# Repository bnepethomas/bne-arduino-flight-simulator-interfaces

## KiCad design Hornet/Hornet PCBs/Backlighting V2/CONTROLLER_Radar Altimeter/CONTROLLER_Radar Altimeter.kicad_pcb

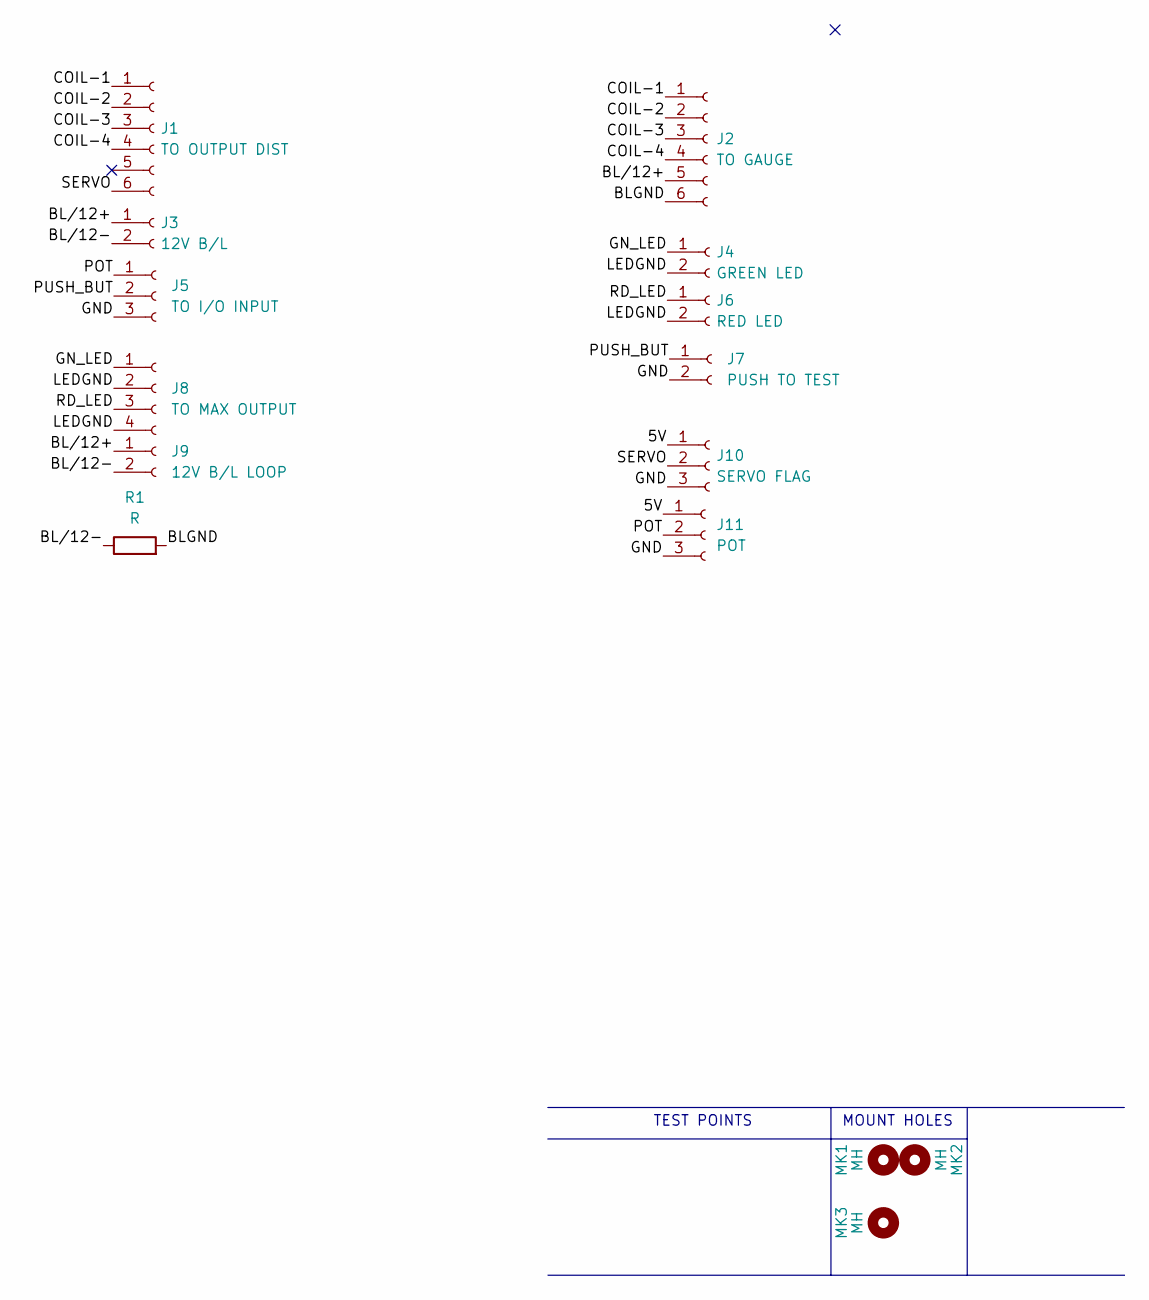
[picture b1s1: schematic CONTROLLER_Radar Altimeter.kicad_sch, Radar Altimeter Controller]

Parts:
J1: TO OUTPUT DIST; Molex_KK-254_AE-6410-06A_1x06_P2.54mm_Vertical
J2: TO GAUGE; Molex_KK-254_AE-6410-06A_1x06_P2.54mm_Vertical
J3: 12V B/L; Molex_KK-254_AE-6410-02A_1x02_P2.54mm_Vertical
J4: GREEN LED; Molex_KK-254_AE-6410-02A_1x02_P2.54mm_Vertical
J5: TO I/O INPUT; Molex_KK-254_AE-6410-03A_1x03_P2.54mm_Vertical
J6: RED LED; Molex_KK-254_AE-6410-02A_1x02_P2.54mm_Vertical
J7: PUSH TO TEST; Molex_KK-254_AE-6410-02A_1x02_P2.54mm_Vertical
J8: TO MAX OUTPUT; Molex_KK-254_AE-6410-04A_1x04_P2.54mm_Vertical
J9: 12V B/L LOOP; Molex_KK-254_AE-6410-02A_1x02_P2.54mm_Vertical
J10: SERVO FLAG; Molex_KK-254_AE-6410-03A_1x03_P2.54mm_Vertical
J11: POT; Molex_KK-254_AE-6410-03A_1x03_P2.54mm_Vertical
MK1, MK2, MK3: MH; MountingHole_2.5mm
R1: R; R_Axial_DIN0204_L3.6mm_D1.6mm_P2.54mm_Vertical

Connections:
/5V: J10.1, J11.1
/BLGND: J2.6, R1.2
/BL/12+: J2.5, J3.1, J9.1
/BL/12-: J3.2, J9.2, R1.1
/COIL-1: J1.1, J2.1
/COIL-2: J1.2, J2.2
/COIL-3: J1.3, J2.3
/COIL-4: J1.4, J2.4
/GND: J5.3, J7.2, J10.3, J11.3
/GN_LED: J4.1, J8.1
/LEDGND: J4.2, J6.2, J8.2, J8.4
/POT: J5.1, J11.2
/PUSH_BUT: J5.2, J7.1
/RD_LED: J6.1, J8.3
/SERVO: J1.6, J10.2

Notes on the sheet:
MOUNT HOLES
TEST POINTS

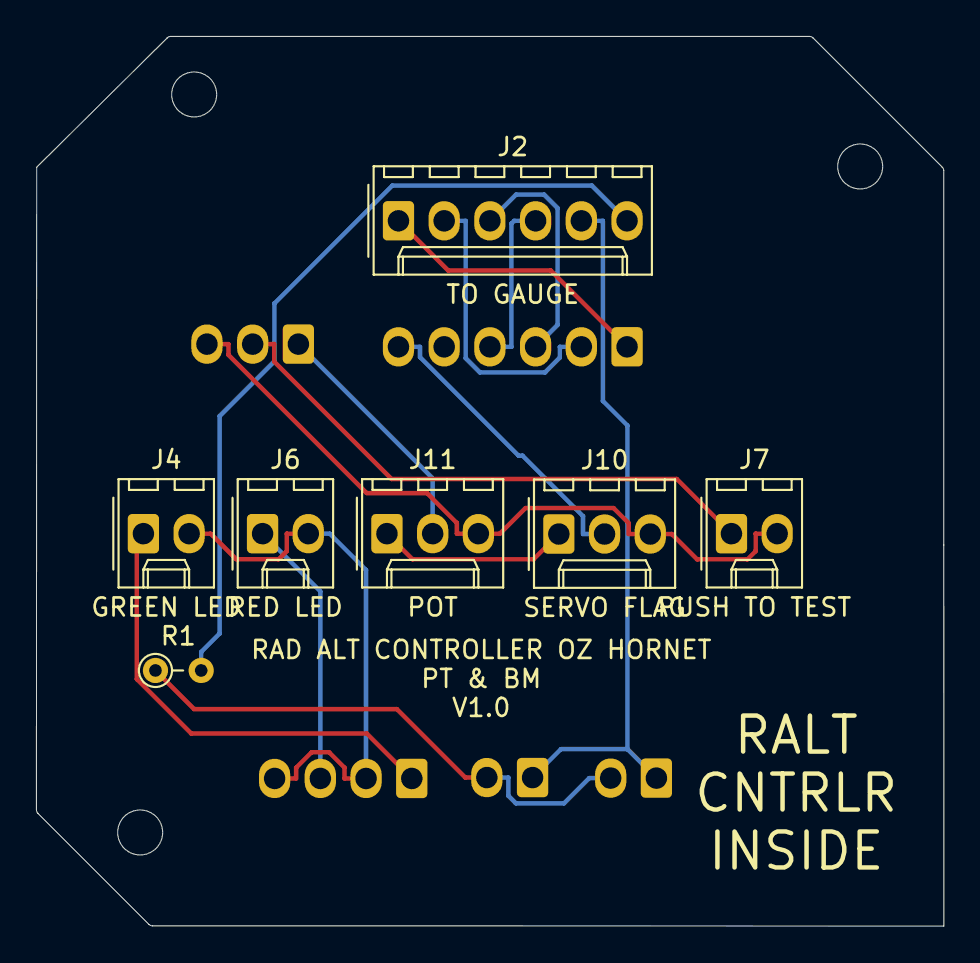
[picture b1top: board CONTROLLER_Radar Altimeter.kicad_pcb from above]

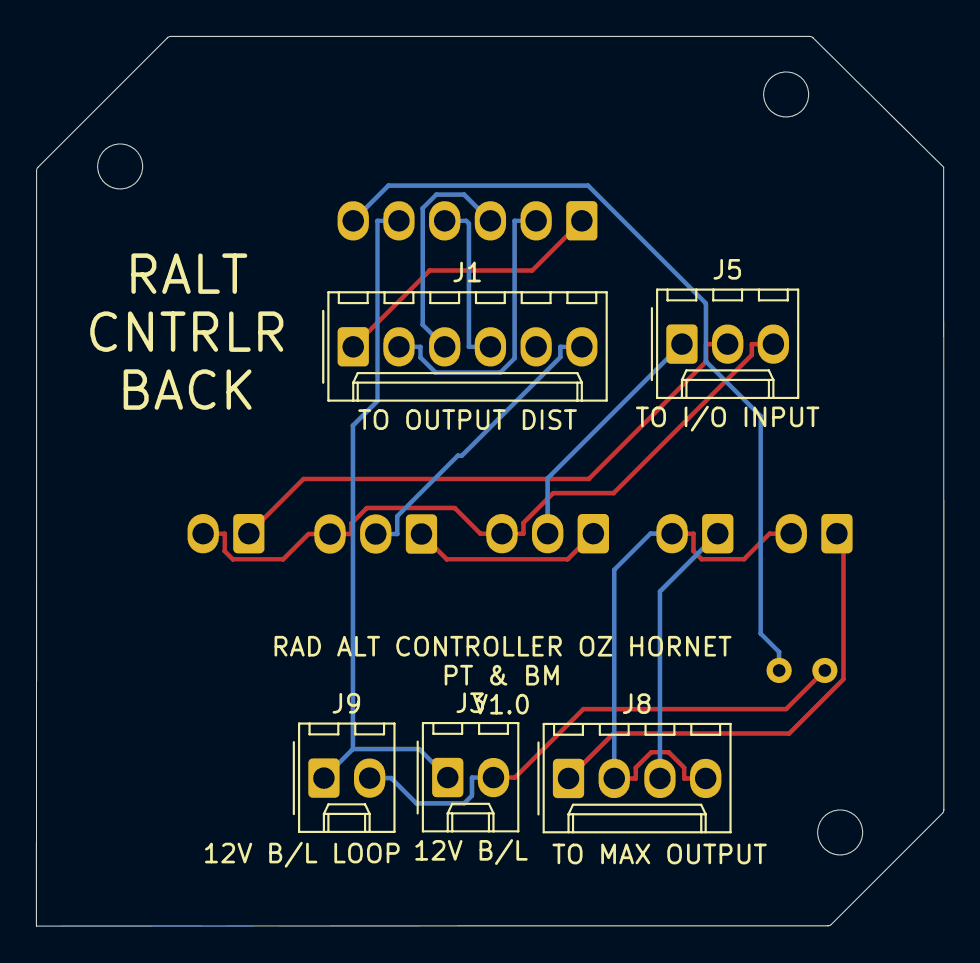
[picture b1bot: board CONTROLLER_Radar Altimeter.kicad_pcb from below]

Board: 2 copper layers, 50.4 x 49.4 mm, 15 parts (5 on the bottom side), 15 nets.

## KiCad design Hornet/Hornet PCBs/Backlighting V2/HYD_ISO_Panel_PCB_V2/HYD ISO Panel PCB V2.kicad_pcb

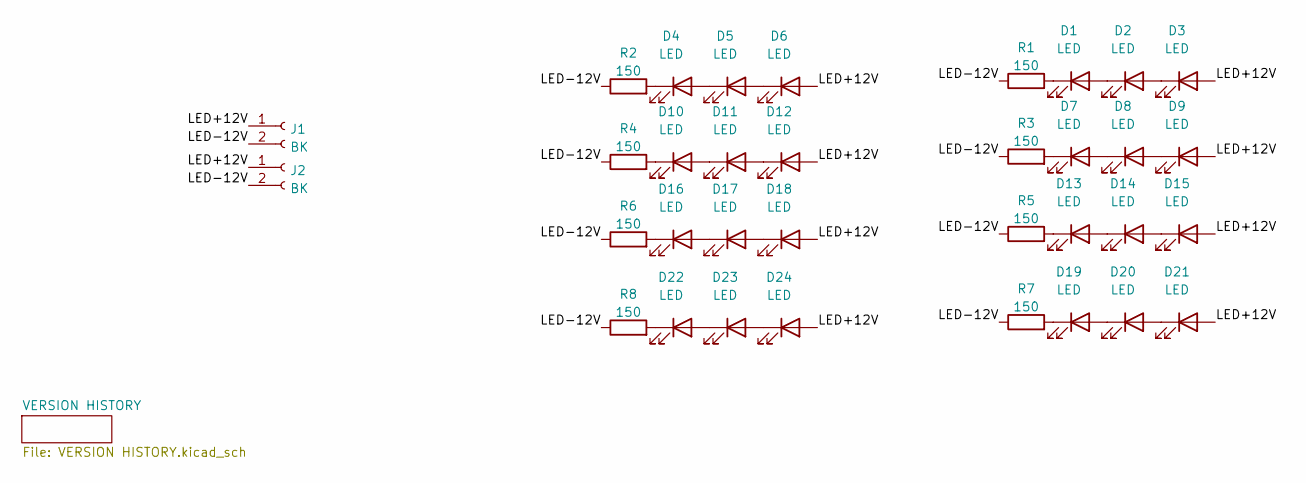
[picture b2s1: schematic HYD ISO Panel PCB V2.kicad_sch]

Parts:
D1, D2, D3, D4, D5, D6, D7, D8, D9, D10, D11, D12, D13, D14, D15, D16, D17, D18, D19, D20, D21, D22, D23, D24: LED; LED_D3.0mm
J1, J2: BK; Molex_KK-254_AE-6410-02A_1x02_P2.54mm_Vertical
R1, R2, R3, R4, R5, R6, R7, R8: 150; R_Axial_DIN0204_L3.6mm_D1.6mm_P2.54mm_Vertical

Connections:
/LED+12V: D3.2 (A), D6.2 (A), D9.2 (A), D12.2 (A), D15.2 (A), D18.2 (A), D21.2 (A), D24.2 (A), J1.1, J2.1
/LED-12V: J1.2, J2.2, R1.1, R2.1, R3.1, R4.1, R5.1, R6.1, R7.1, R8.1
unnamed: D1.1 (K), R1.2
unnamed: D1.2 (A), D2.1 (K)
unnamed: D2.2 (A), D3.1 (K)
unnamed: D4.1 (K), R2.2
unnamed: D4.2 (A), D5.1 (K)
unnamed: D5.2 (A), D6.1 (K)
unnamed: D7.1 (K), R3.2
unnamed: D7.2 (A), D8.1 (K)
unnamed: D8.2 (A), D9.1 (K)
unnamed: D10.1 (K), R4.2
unnamed: D10.2 (A), D11.1 (K)
unnamed: D11.2 (A), D12.1 (K)
unnamed: D13.1 (K), R5.2
unnamed: D13.2 (A), D14.1 (K)
unnamed: D14.2 (A), D15.1 (K)
unnamed: D16.1 (K), R6.2
unnamed: D16.2 (A), D17.1 (K)
unnamed: D17.2 (A), D18.1 (K)
unnamed: D19.1 (K), R7.2
unnamed: D19.2 (A), D20.1 (K)
unnamed: D20.2 (A), D21.1 (K)
unnamed: D22.1 (K), R8.2
unnamed: D22.2 (A), D23.1 (K)
unnamed: D23.2 (A), D24.1 (K)

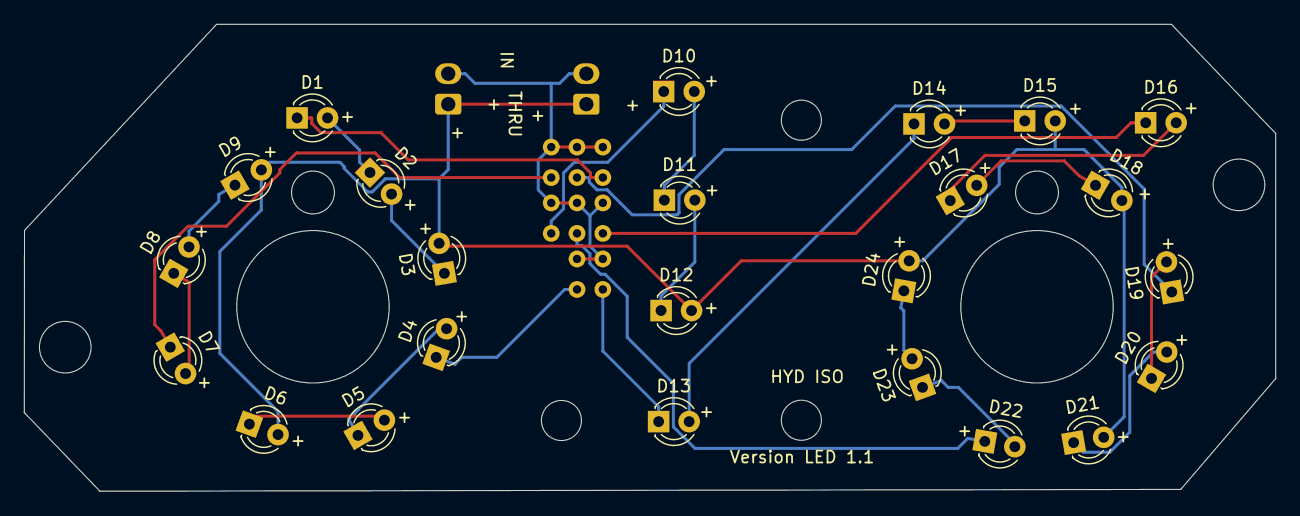
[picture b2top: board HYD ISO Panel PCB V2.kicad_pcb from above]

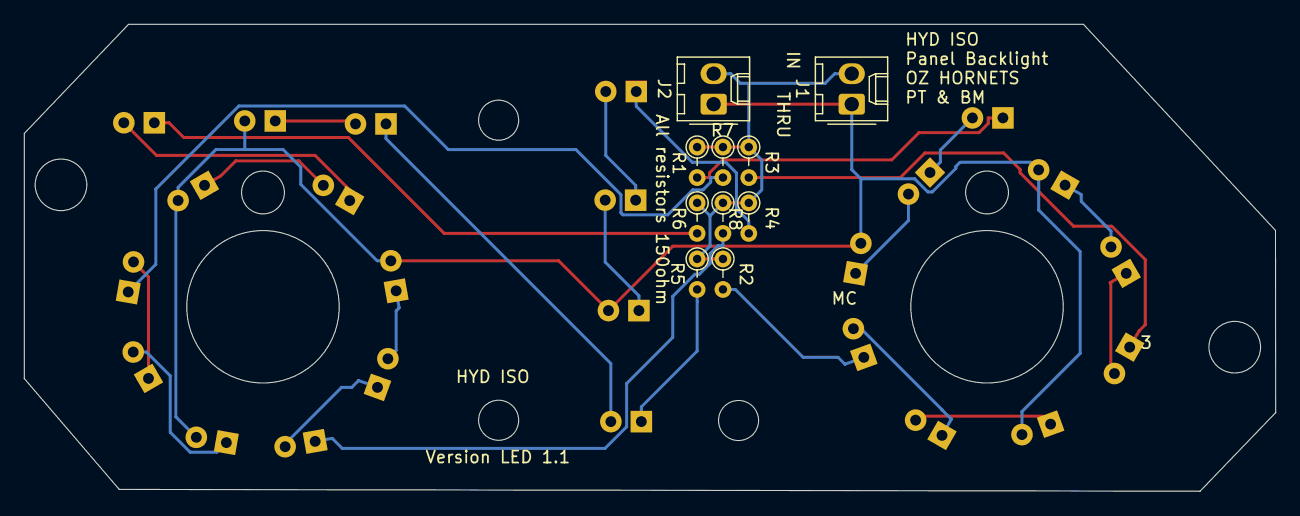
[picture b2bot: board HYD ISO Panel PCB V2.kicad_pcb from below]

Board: 2 copper layers, 104.3 x 38.9 mm, 38 parts (10 on the bottom side), 26 nets.

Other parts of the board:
REF01, REF02: OH_Panel_Fastner_Keepout; OH_Panel_6-32_PHS
REF03, REF04: 100SPX_Toggle_13mm_x_18mm

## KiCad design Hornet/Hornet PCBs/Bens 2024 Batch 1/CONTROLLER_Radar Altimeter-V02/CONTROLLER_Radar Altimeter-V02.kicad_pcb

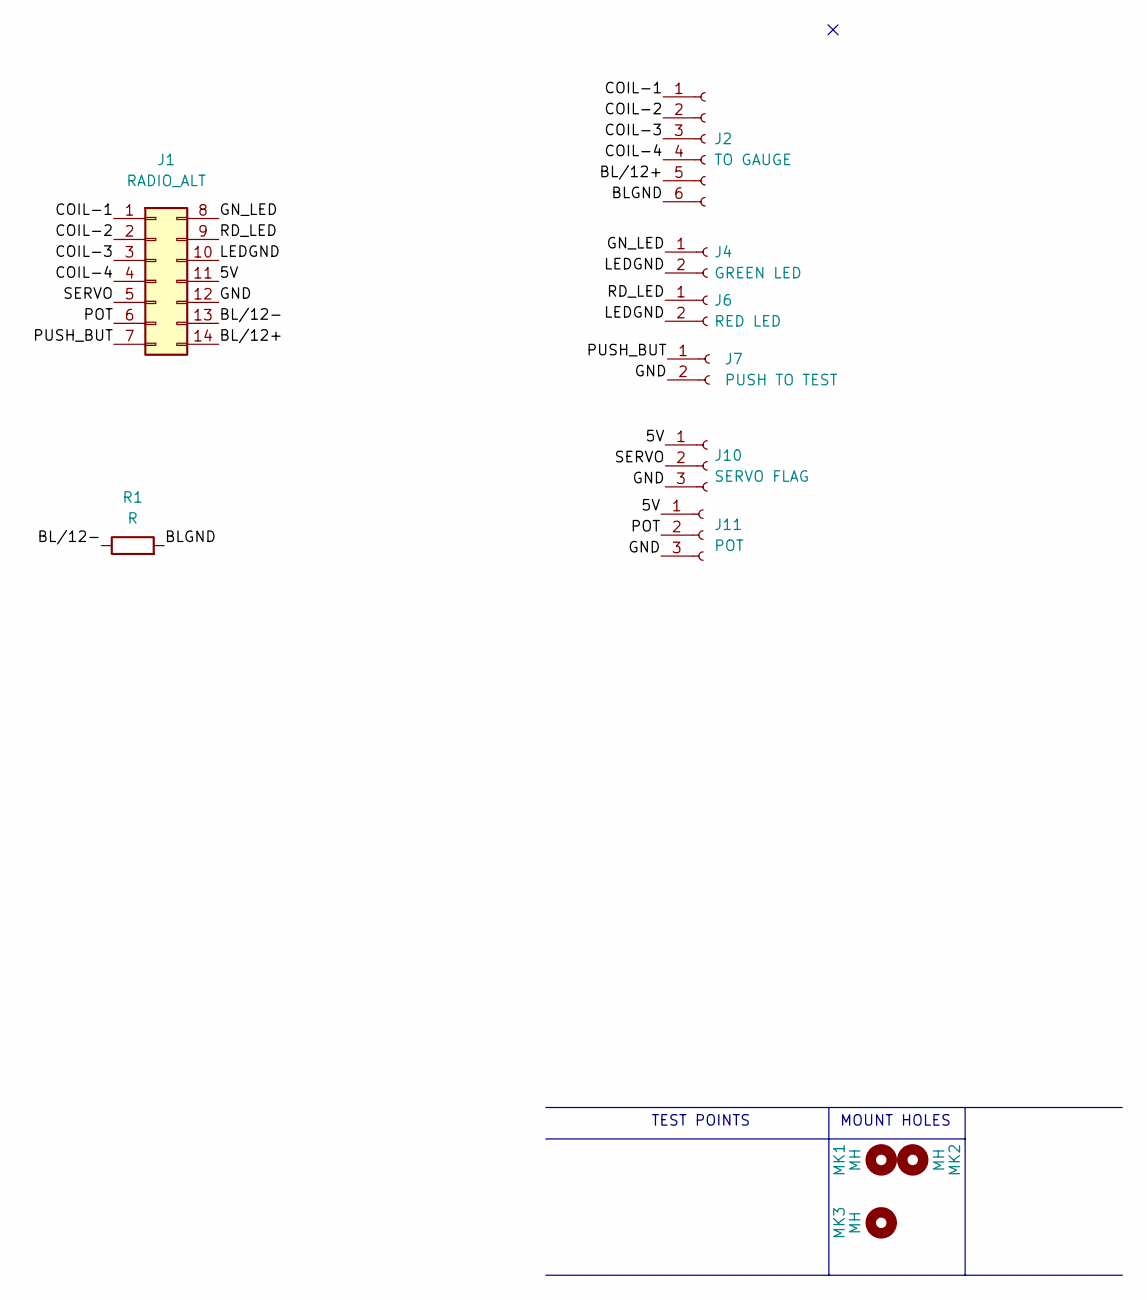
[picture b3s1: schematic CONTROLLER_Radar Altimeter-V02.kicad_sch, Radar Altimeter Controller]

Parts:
J1: RADIO_ALT; IDC-Header_2x07_P2.54mm_Vertical
J2: TO GAUGE; Molex_KK-254_AE-6410-06A_1x06_P2.54mm_Vertical
J4: GREEN LED; Molex_KK-254_AE-6410-02A_1x02_P2.54mm_Vertical
J6: RED LED; Molex_KK-254_AE-6410-02A_1x02_P2.54mm_Vertical
J7: PUSH TO TEST; Molex_KK-254_AE-6410-02A_1x02_P2.54mm_Vertical
J10: SERVO FLAG; Molex_KK-254_AE-6410-03A_1x03_P2.54mm_Vertical
J11: POT; Molex_KK-254_AE-6410-03A_1x03_P2.54mm_Vertical
MK1, MK2, MK3: MH; MountingHole_2.5mm
R1: R; R_Axial_DIN0204_L3.6mm_D1.6mm_P2.54mm_Vertical

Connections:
/5V: J1.11, J10.1, J11.1
/BLGND: J2.6, R1.2
/BL/12+: J1.14, J2.5
/BL/12-: J1.13, R1.1
/COIL-1: J1.1, J2.1
/COIL-2: J1.2, J2.2
/COIL-3: J1.3, J2.3
/COIL-4: J1.4, J2.4
/GND: J1.12, J7.2, J10.3, J11.3
/GN_LED: J1.8, J4.1
/LEDGND: J1.10, J4.2, J6.2
/POT: J1.6, J11.2
/PUSH_BUT: J1.7, J7.1
/RD_LED: J1.9, J6.1
/SERVO: J1.5, J10.2

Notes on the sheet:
MOUNT HOLES
TEST POINTS

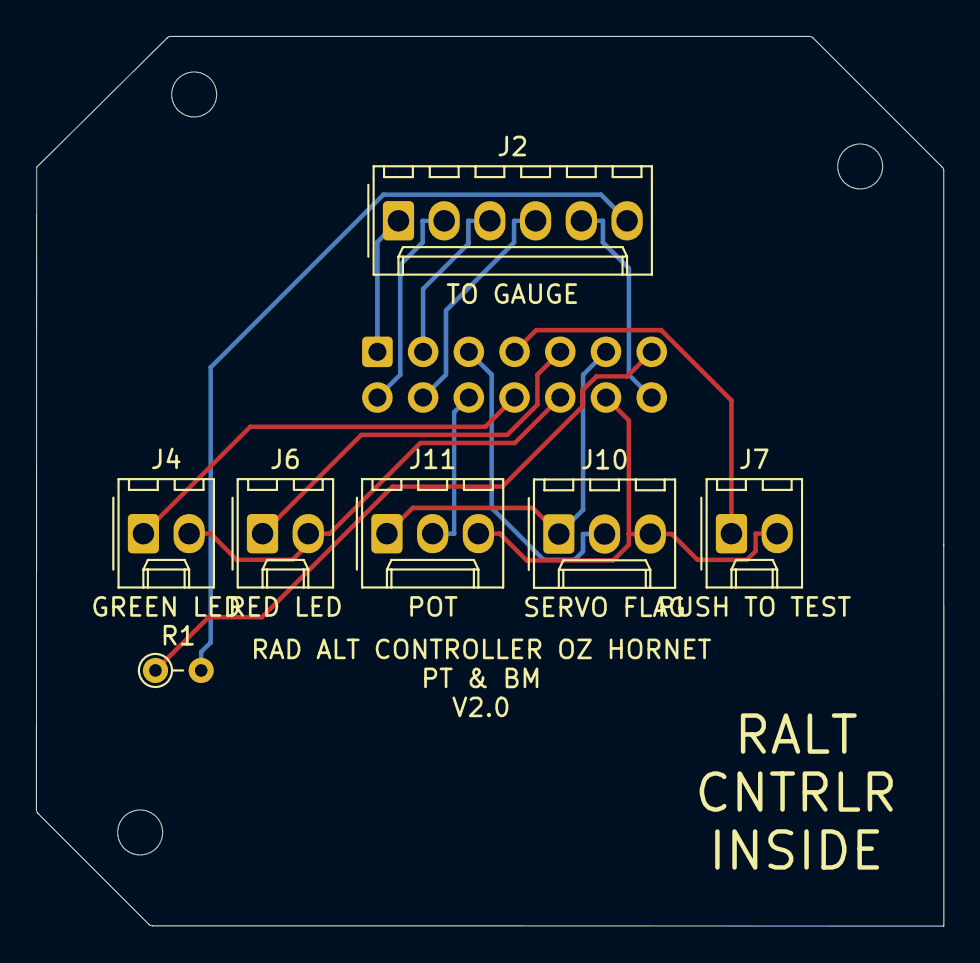
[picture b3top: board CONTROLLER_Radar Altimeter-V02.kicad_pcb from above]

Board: 2 copper layers, 50.4 x 49.4 mm, 11 parts (1 on the bottom side), 15 nets.

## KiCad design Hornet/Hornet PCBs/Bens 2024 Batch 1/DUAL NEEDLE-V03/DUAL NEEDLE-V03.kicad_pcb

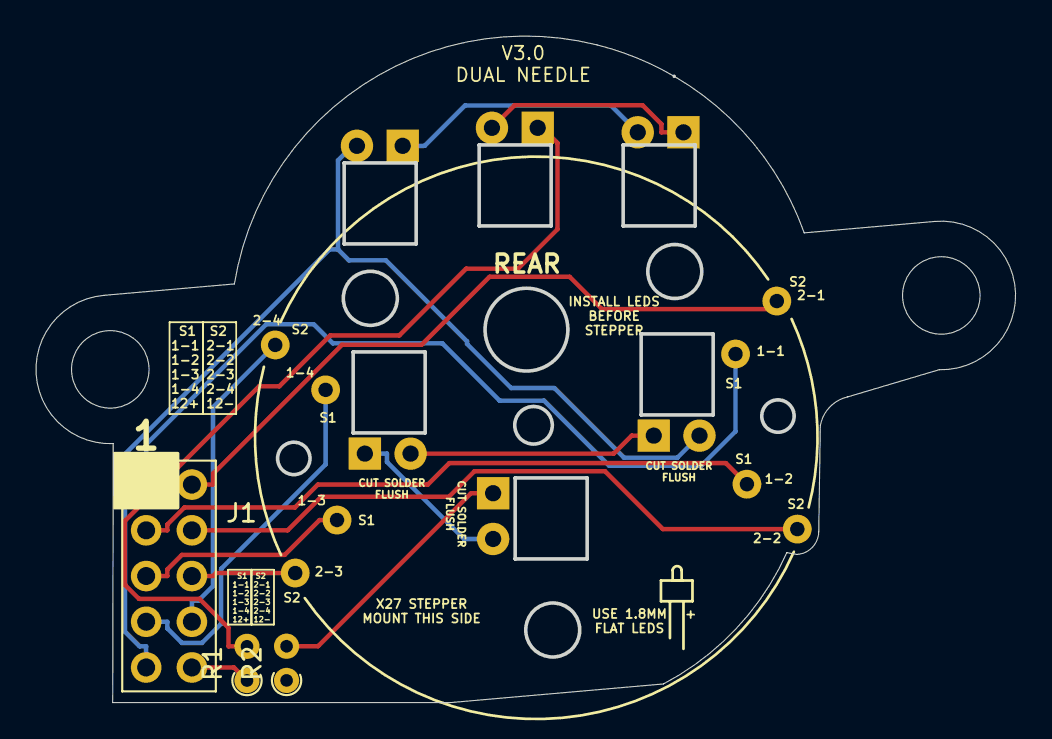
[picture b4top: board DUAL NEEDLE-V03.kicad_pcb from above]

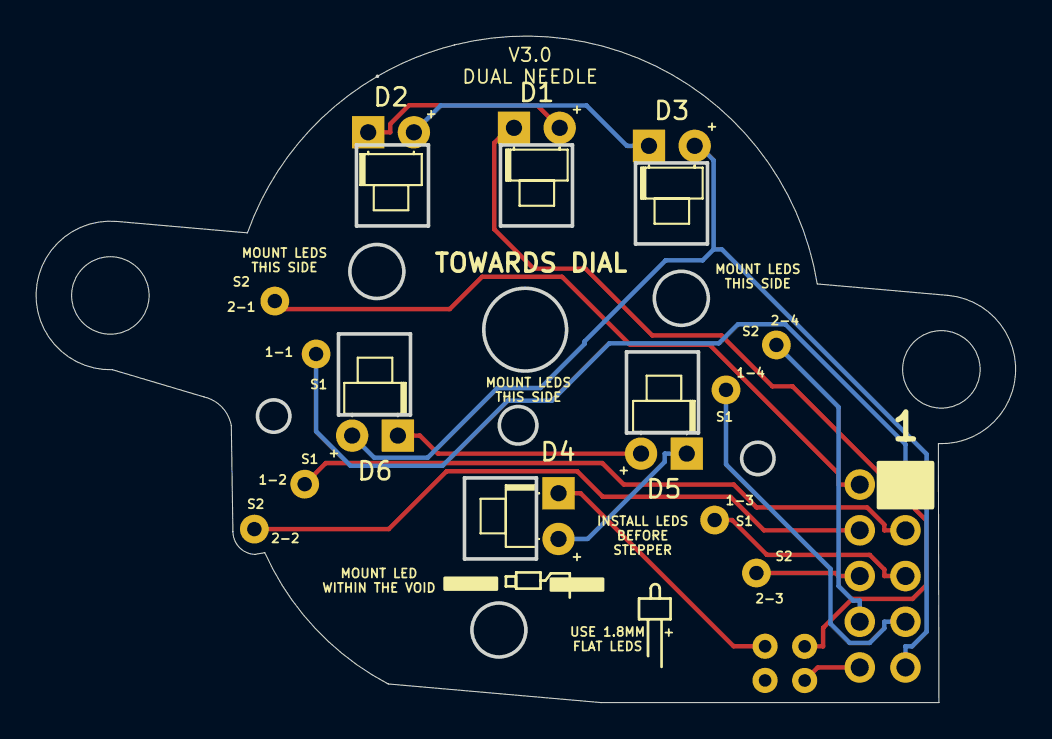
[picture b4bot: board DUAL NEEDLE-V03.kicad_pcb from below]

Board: 2 copper layers, 54.4 x 37.0 mm, 10 parts (7 on the bottom side), 16 nets.

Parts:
D1, D2, D3, D4, D5, D6: LED; LED_D1.8mm_W1.8mm_H2.4mm_Horizontal_O1.27mm_Z1.6mm-OH
J1: Conn_02x05_Top_Bottom; PinHeader_2x05_P2.54mm_Vertical
R1, R2: R; R_Axial_DIN0204_L3.6mm_D1.6mm_P1.90mm_Vertical
U1: X40-stepper-gkl_misc; X40-stepper

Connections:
/LED+12V: D3.2 (A), D6.2 (A), J1.9
/LED-12V: J1.10, R1.1
/STEPPER-1-1: J1.1, U1.1
/STEPPER-1-2: J1.3, U1.2
/STEPPER-1-3: J1.5, U1.3
/STEPPER-1-4: J1.7, U1.4
/STEPPER-2-1: J1.2, U1.5
/STEPPER-2-2: J1.4, U1.6
/STEPPER-2-3: J1.6, U1.7
/STEPPER-2-4: J1.8, U1.8
unnamed: D1.1 (K), R1.2
unnamed: D1.2 (A), D2.1 (K)
unnamed: D2.2 (A), D3.1 (K)
unnamed: D4.1 (K), R2.2
unnamed: D4.2 (A), D5.1 (K)
unnamed: D5.2 (A), D6.1 (K)

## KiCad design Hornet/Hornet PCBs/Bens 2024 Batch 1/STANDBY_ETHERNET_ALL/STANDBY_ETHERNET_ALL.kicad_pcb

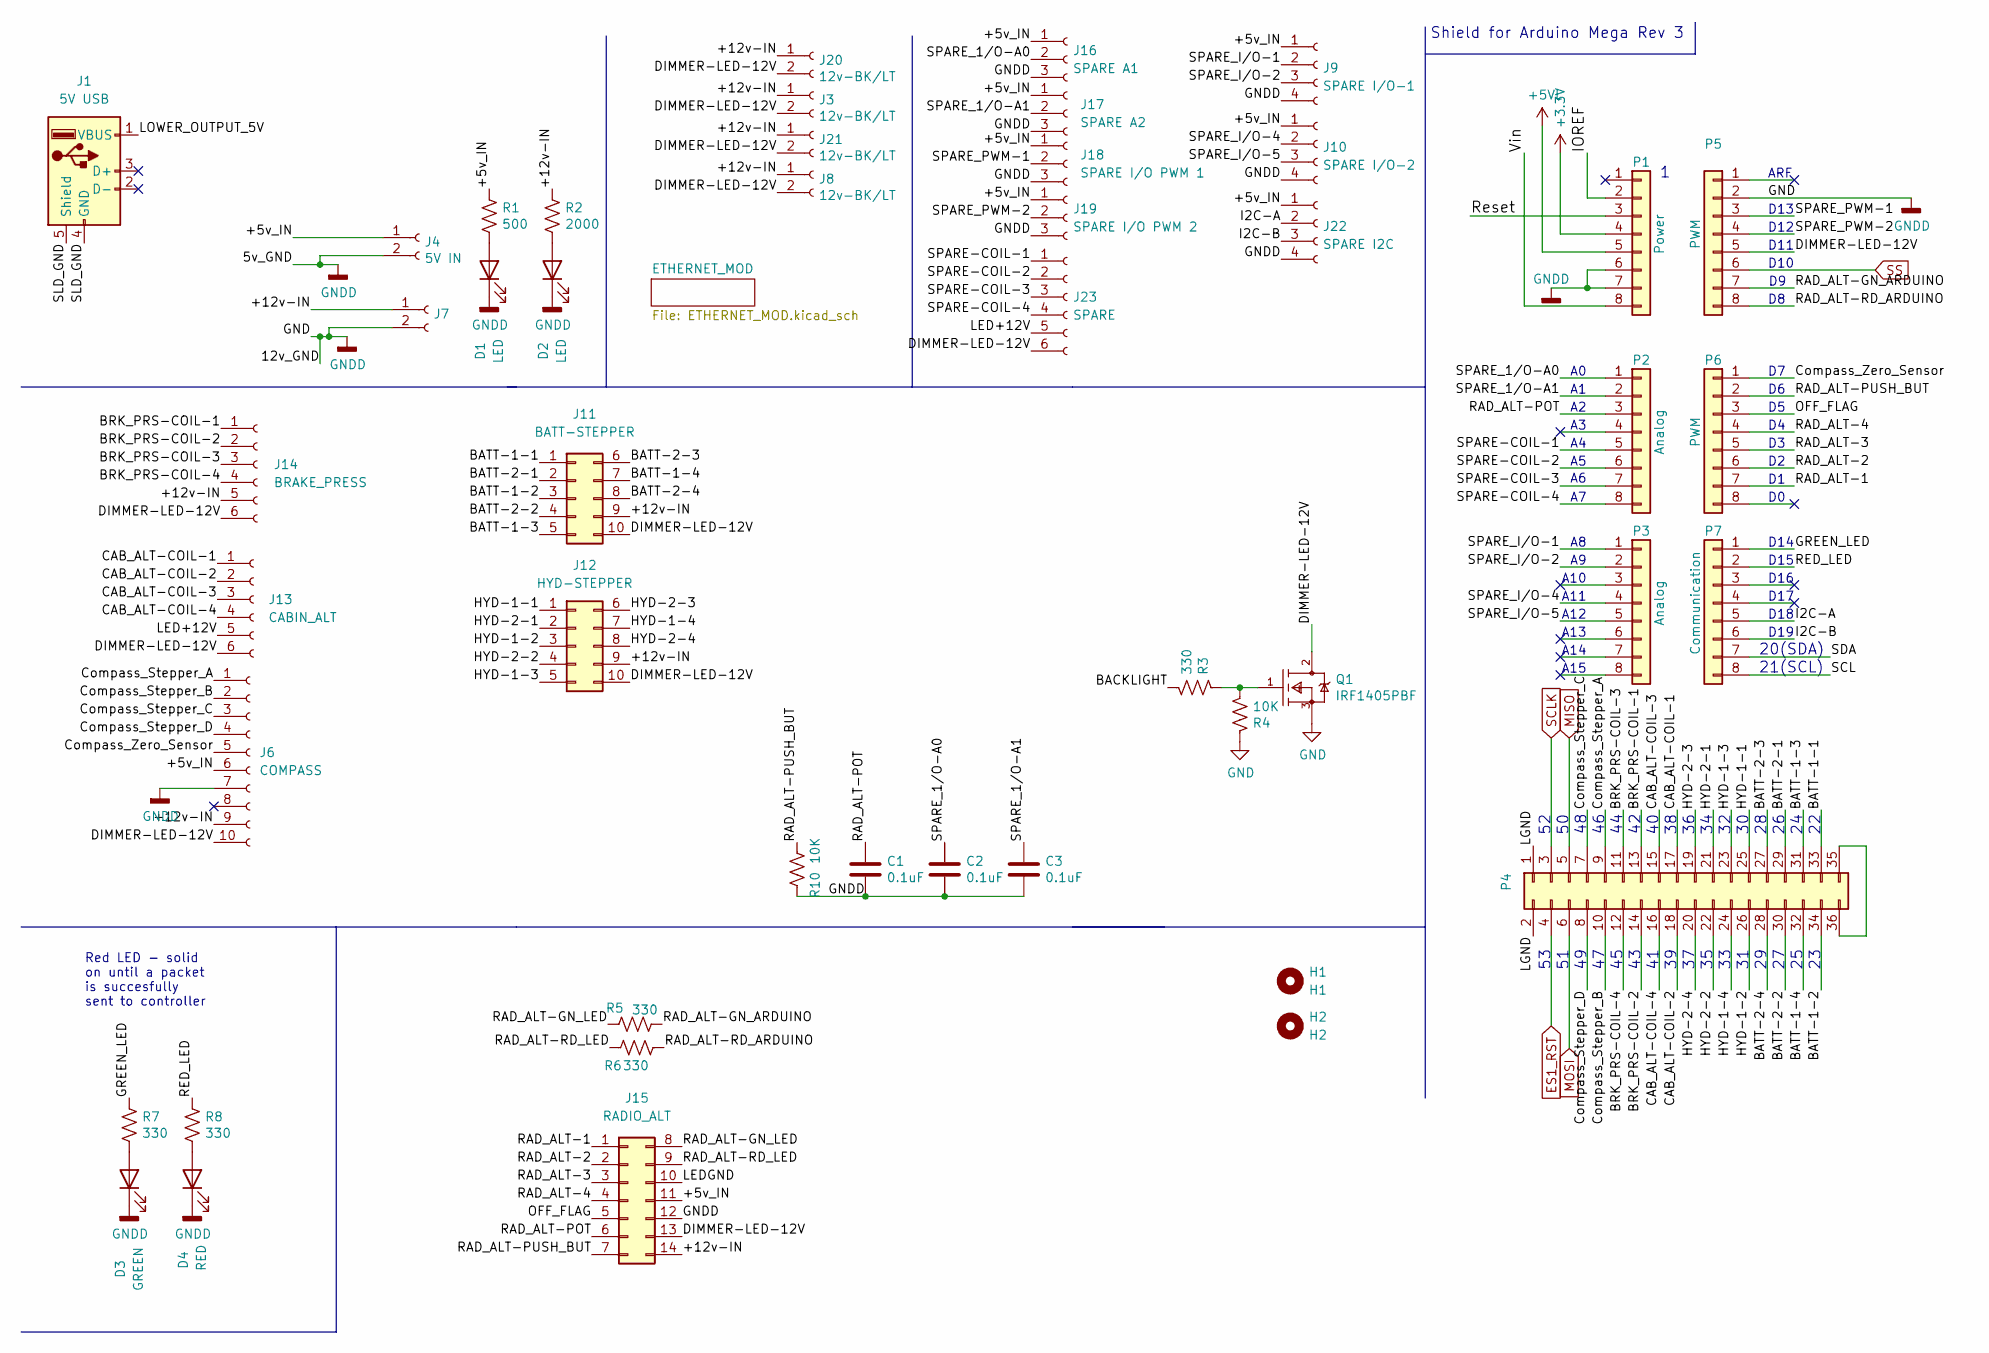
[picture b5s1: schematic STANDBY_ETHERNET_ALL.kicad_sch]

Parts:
C1, C2, C3: 0.1uF; C_Disc_D6.0mm_W2.5mm_P5.00mm
D1, D2: LED; LED_D3.0mm
D3: GREEN; LED_D3.0mm
D4: RED; LED_D3.0mm
H1: H1; MountingHole_2.5mm
H2: H2; MountingHole_2.5mm
J1: 5V USB; USB_A_Molex_67643_Horizontal
J3, J8, J20, J21: 12v-BK/LT; Molex_KK-254_AE-6410-02A_1x02_P2.54mm_Vertical
J4: 5V IN; BarrelJack_Horizontal
J6: COMPASS; Molex_KK-254_AE-6410-10A_1x10_P2.54mm_Vertical
J7: STEPPER IN 12-20VDC; BarrelJack_Horizontal
J9: SPARE I/O-1; Molex_KK-254_AE-6410-04A_1x04_P2.54mm_Vertical
J10: SPARE I/O-2; Molex_KK-254_AE-6410-04A_1x04_P2.54mm_Vertical
J11: BATT-STEPPER; IDC-Header_2x05_P2.54mm_Vertical
J12: HYD-STEPPER; IDC-Header_2x05_P2.54mm_Vertical
J13: CABIN_ALT; Molex_KK-254_AE-6410-06A_1x06_P2.54mm_Vertical
J14: BRAKE_PRESS; Molex_KK-254_AE-6410-06A_1x06_P2.54mm_Vertical
J15: RADIO_ALT; IDC-Header_2x07_P2.54mm_Vertical
J16: SPARE A1; Molex_KK-254_AE-6410-03A_1x03_P2.54mm_Vertical
J17: SPARE A2; Molex_KK-254_AE-6410-03A_1x03_P2.54mm_Vertical
J18: SPARE I/O PWM 1; Molex_KK-254_AE-6410-03A_1x03_P2.54mm_Vertical
J19: SPARE I/O PWM 2; Molex_KK-254_AE-6410-03A_1x03_P2.54mm_Vertical
J22: SPARE I2C; Molex_KK-254_AE-6410-04A_1x04_P2.54mm_Vertical
J23: SPARE; Molex_KK-254_AE-6410-06A_1x06_P2.54mm_Vertical
P1: Power; Socket_Strip_Arduino_1x08
P2, P3: Analog; Socket_Strip_Arduino_1x08
P4: Digital; Socket_Strip_Arduino_2x18
P5, P6: PWM; Socket_Strip_Arduino_1x08
P7: Communication; Socket_Strip_Arduino_1x08
Q1: IRF1405PBF; TO-220-3_Vertical; mouser part number 942-IRF1405PBF; digikey description MOSFET N-CH 55V 169A TO-220AB
R1: 500; R_Axial_DIN0204_L3.6mm_D1.6mm_P2.54mm_Vertical
R2: 2000; R_Axial_DIN0204_L3.6mm_D1.6mm_P2.54mm_Vertical
R3, R5, R6, R7, R8: 330; R_Axial_DIN0204_L3.6mm_D1.6mm_P2.54mm_Vertical
R4, R10: 10K; R_Axial_DIN0204_L3.6mm_D1.6mm_P2.54mm_Vertical

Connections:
+5VL: P1.5
/+5v_IN: J4.1, J6.6, J9.1, J10.1, J15.11, J16.1, J17.1, J18.1, J19.1, J22.1, R1.1
/+12v-IN: J3.1, J6.9, J7.1, J8.1, J11.9, J12.9, J14.5, J15.14, J20.1, J21.1, R2.1
/BACKLIGHT: R3.2
/BATT-1-1: J11.1, P4.33
/BATT-1-2: J11.3, P4.34
/BATT-1-3: J11.5, P4.31
/BATT-1-4: J11.7, P4.32
/BATT-2-1: J11.2, P4.29
/BATT-2-2: J11.4, P4.30
/BATT-2-3: J11.6, P4.27
/BATT-2-4: J11.8, P4.28
/BRK_PRS-COIL-1: J14.1, P4.13
/BRK_PRS-COIL-2: J14.2, P4.14
/BRK_PRS-COIL-3: J14.3, P4.11
/BRK_PRS-COIL-4: J14.4, P4.12
/CAB_ALT-COIL-1: J13.1, P4.17
/CAB_ALT-COIL-2: J13.2, P4.18
/CAB_ALT-COIL-3: J13.3, P4.15
/CAB_ALT-COIL-4: J13.4, P4.16
/Compass_Stepper_A: J6.1, P4.9
/Compass_Stepper_B: J6.2, P4.10
/Compass_Stepper_C: J6.3, P4.7
/Compass_Stepper_D: J6.4, P4.8
/Compass_Zero_Sensor: J6.5, P6.1
/DIMMER-LED-12V: J3.2, J6.10, J8.2, J11.10, J12.10, J13.6, J14.6, J15.13, J20.2, J21.2, J23.6, P5.5, Q1.2 (D)
/GREEN_LED: P7.1, R7.1
/HYD-1-1: J12.1, P4.25
/HYD-1-2: J12.3, P4.26
/HYD-1-3: J12.5, P4.23
/HYD-1-4: J12.7, P4.24
/HYD-2-1: J12.2, P4.21
/HYD-2-2: J12.4, P4.22
/HYD-2-3: J12.6, P4.19
/HYD-2-4: J12.8, P4.20
/I2C-A: J22.2, P7.5
/I2C-B: J22.3, P7.6
/IOREF: P1.2
/LED+12V: J13.5, J23.5
/LEDGND: J15.10
/LGND: P4.1, P4.2
/LOWER_OUTPUT_5V: J1.1 (VBUS)
/OFF_FLAG: J15.5, P6.3
/RAD_ALT-1: J15.1, P6.7
/RAD_ALT-2: J15.2, P6.6
/RAD_ALT-3: J15.3, P6.5
/RAD_ALT-4: J15.4, P6.4
/RAD_ALT-GN_ARDUINO: P5.7, R5.2
/RAD_ALT-GN_LED: J15.8, R5.1
/RAD_ALT-POT: C1.1, J15.6, P2.3
/RAD_ALT-PUSH_BUT: J15.7, P6.2, R10.2
/RAD_ALT-RD_ARDUINO: P5.8, R6.2
/RAD_ALT-RD_LED: J15.9, R6.1
/RED_LED: P7.2, R8.1
/Reset: P1.3
/SCL: P7.8
/SDA: P7.7
/SLD_GND: J1.4 (GND), J1.5 (Shield)
/SPARE-COIL-1: J23.1, P2.5
/SPARE-COIL-2: J23.2, P2.6
/SPARE-COIL-3: J23.3, P2.7
/SPARE-COIL-4: J23.4, P2.8
/SPARE_1/O-A0: C2.1, J16.2, P2.1
/SPARE_1/O-A1: C3.1, J17.2, P2.2
/SPARE_I/O-1: J9.2, P3.1
/SPARE_I/O-2: J9.3, P3.2
/SPARE_I/O-4: J10.2, P3.4
/SPARE_I/O-5: J10.3, P3.5
/SPARE_PWM-1: J18.2, P5.3
/SPARE_PWM-2: J19.2, P5.4
/Vin: P1.8
ES1_RST: P4.4; also elsewhere on the board
MISO: P4.5; also elsewhere on the board
MOSI: P4.6; also elsewhere on the board
unnamed: D1.2 (A), R1.2
unnamed: D2.2 (A), R2.2
unnamed: D3.2 (A), R7.2
unnamed: D4.2 (A), R8.2
unnamed: P4.35, P4.36
unnamed: Q1.1 (G), R3.1, R4.2
SCLK: P4.3; also elsewhere on the board
SS: P5.6; also elsewhere on the board

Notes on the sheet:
A14
ARF
Shield for Arduino Mega Rev 3
D10
D13
Red LED - solid on until a packet is succesfully sent to controller
A13
A12
D14
A15
D15
D12
A11
D17
D11
20(SDA)
21(SCL)
D19
D16
A10
D18

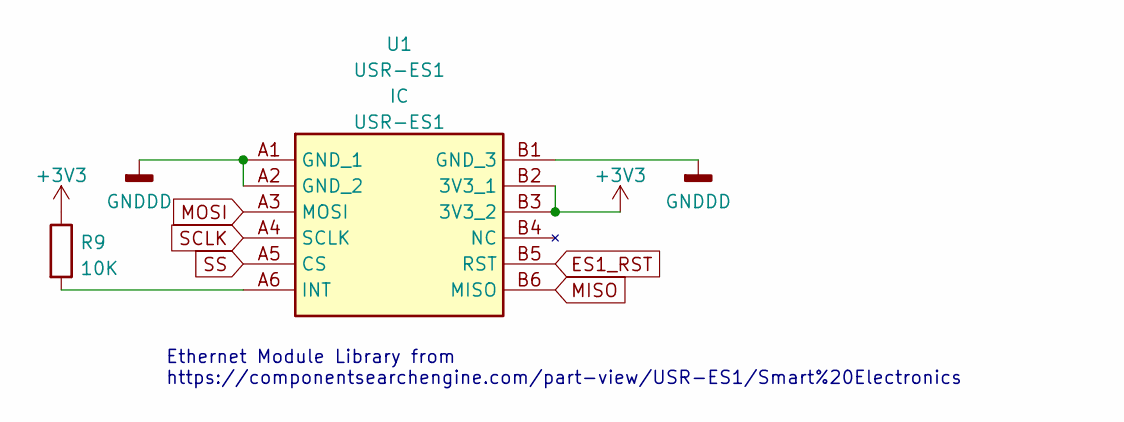
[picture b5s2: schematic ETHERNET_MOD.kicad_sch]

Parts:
R9: 10K; R_Axial_DIN0204_L3.6mm_D1.6mm_P2.54mm_Vertical
U1: USR-ES1; USRES1; Manufacturer_Part_Number USR-ES1

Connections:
ES1_RST: U1.B5 (RST); also elsewhere on the board
MISO: U1.B6 (MISO); also elsewhere on the board
MOSI: U1.A3 (MOSI); also elsewhere on the board
unnamed: R9.2, U1.A6 (INT)
SCLK: U1.A4 (SCLK); also elsewhere on the board
SS: U1.A5 (CS); also elsewhere on the board

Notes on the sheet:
Ethernet Module Library from https://componentsearchengine.com/part-view/USR-ES1/Smart%20Electronics

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
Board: 2 copper layers, 49 parts (0 on the bottom side), 76 nets, no tracks yet.

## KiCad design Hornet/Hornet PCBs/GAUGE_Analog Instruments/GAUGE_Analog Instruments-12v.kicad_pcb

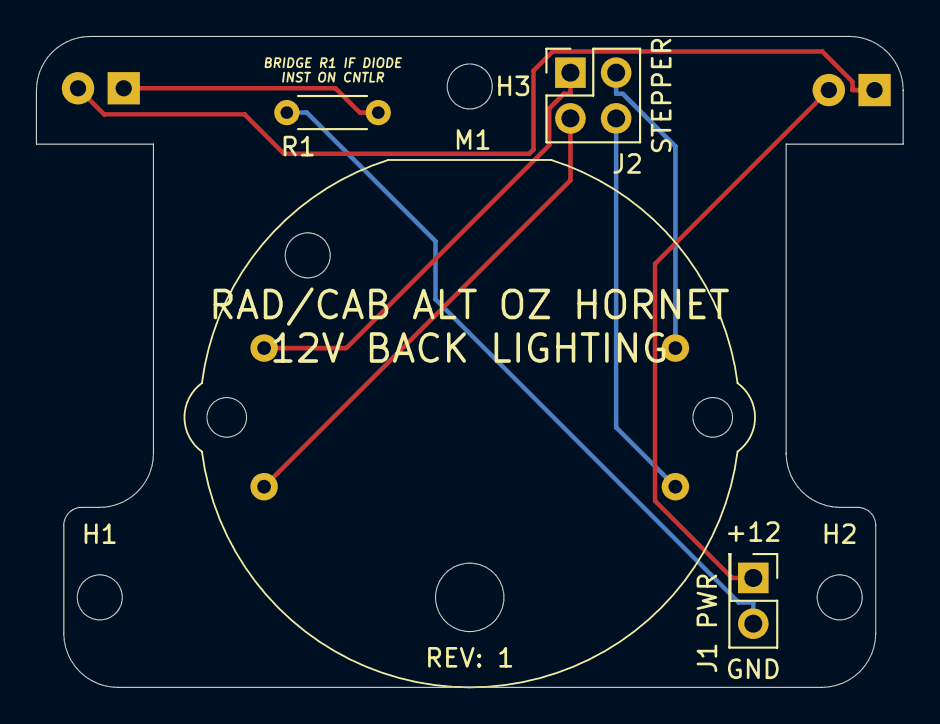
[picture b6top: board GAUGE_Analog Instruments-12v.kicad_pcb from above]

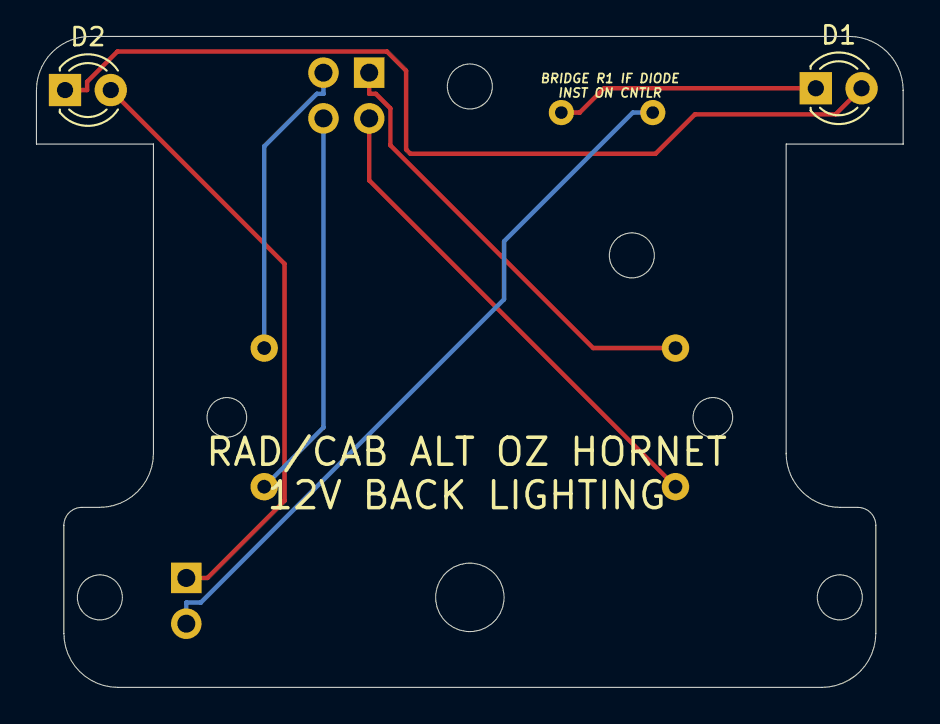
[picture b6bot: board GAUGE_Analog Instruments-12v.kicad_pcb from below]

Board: 2 copper layers, 48.2 x 36.2 mm, 9 parts (2 on the bottom side), 8 nets.

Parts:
D1, D2: LED; LED_D3.0mm
H1, H2, H3: MountingHole; MountingHole_2.5mm
J1: PWR; PinHeader_2x01_P2.54mm_Vertical
J2: STEPPER; PinHeader_2x02_P2.54mm_Vertical
M1: VID29-02
R1: R; R_Axial_DIN0204_L3.6mm_D1.6mm_P5.08mm_Horizontal

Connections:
/COIL1: J2.1, M1.1
/COIL2: J2.3, M1.2 (-)
/COIL3: J2.4, M1.3
/COIL4: J2.2, M1.4
/LED+12V: D2.2 (A), J1.1
/LED-12V: J1.2, R1.1
unnamed: D1.1 (K), R1.2
unnamed: D1.2 (A), D2.1 (K)

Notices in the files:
Hornet/Hornet PCBs/Backlighting V2/CONTROLLER_Radar Altimeter/CONTROLLER_Radar Altimeter.kicad_pcb:
CC BY-NC-SA
